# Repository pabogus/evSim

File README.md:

# Project evSim 
## Purpose description
Simulate a ev connected to a Wallbox for testing purposes.

For testing the behaviour of a AC walbox, respecively charging station, for e-mobility a car simulator is needed.
This project aims to provide such a simulator. In addition for test automation this simulator can be controlled via modbus protocoll using a RS485 connection.
You should be aware about the ISO states and the underlying physical protocoll used on the CS and PP line of a type-2 conector.

The project uses a attiny1616 controller to switch a couple of relays to simulate the voltage levels on the signal lines.
The relais are driven by a TPIC6B595 shift register which has the capability to drive the relays.
The RS485 lines are driven by a MAX 485 ECSA transmitter. The PWM is injected via an optocoppler  LTV 817B.

## As user interface there are:
Two buttons to switch states and cable attributes
An OLED display for the states and the measured PWM duty cycle
ws2812 like LED stripe also to indicate states and PWM duty cycle, respectively the current level.

## Schematic and PCB:
The project contains also a schematic and a PCB in KiCad format with the following features:
The evSim contains also an additional FET incl. a flyback diode, to drive an external releay, e.g. to switch the Walbox on and off.
The evSim provides an additional input at the plug connector intended for current on check.
The evSim contains two simulatior entities to be able to test a twin wallbox.
The evSim contains a voltage regulator for 5V to be independant of the power supply.
The evSim contains a coding switch for the modbus-ID.

For connection screw connectors are used.

### Note:
Currently this is done as a prototype and for usage in a real test environment the following improvements could be done.
- Add some more Cs or Ls for hardening against radiation and spikes.
- Add bigger voltage regulator, or use a tree pin DC/DC converter.
- Make PCB a bit larger, avoid SMD on the backside, add proper conector for power, Modbus and additional functions.

## Not tested/implemented yet:
Additional FET
Selection of modbus-ID via coding switch. Idea is to double use some GPIO lines and read the input at start-up.
Some supporting modbus registers.
Read in voltage on phase L1 with FinA/FinB, just with an opto and capacitive devider to be able to check that the walbox has realy turned on power. (But caution here you touch high volate, I would place the opto and devider on a separate small PCB)

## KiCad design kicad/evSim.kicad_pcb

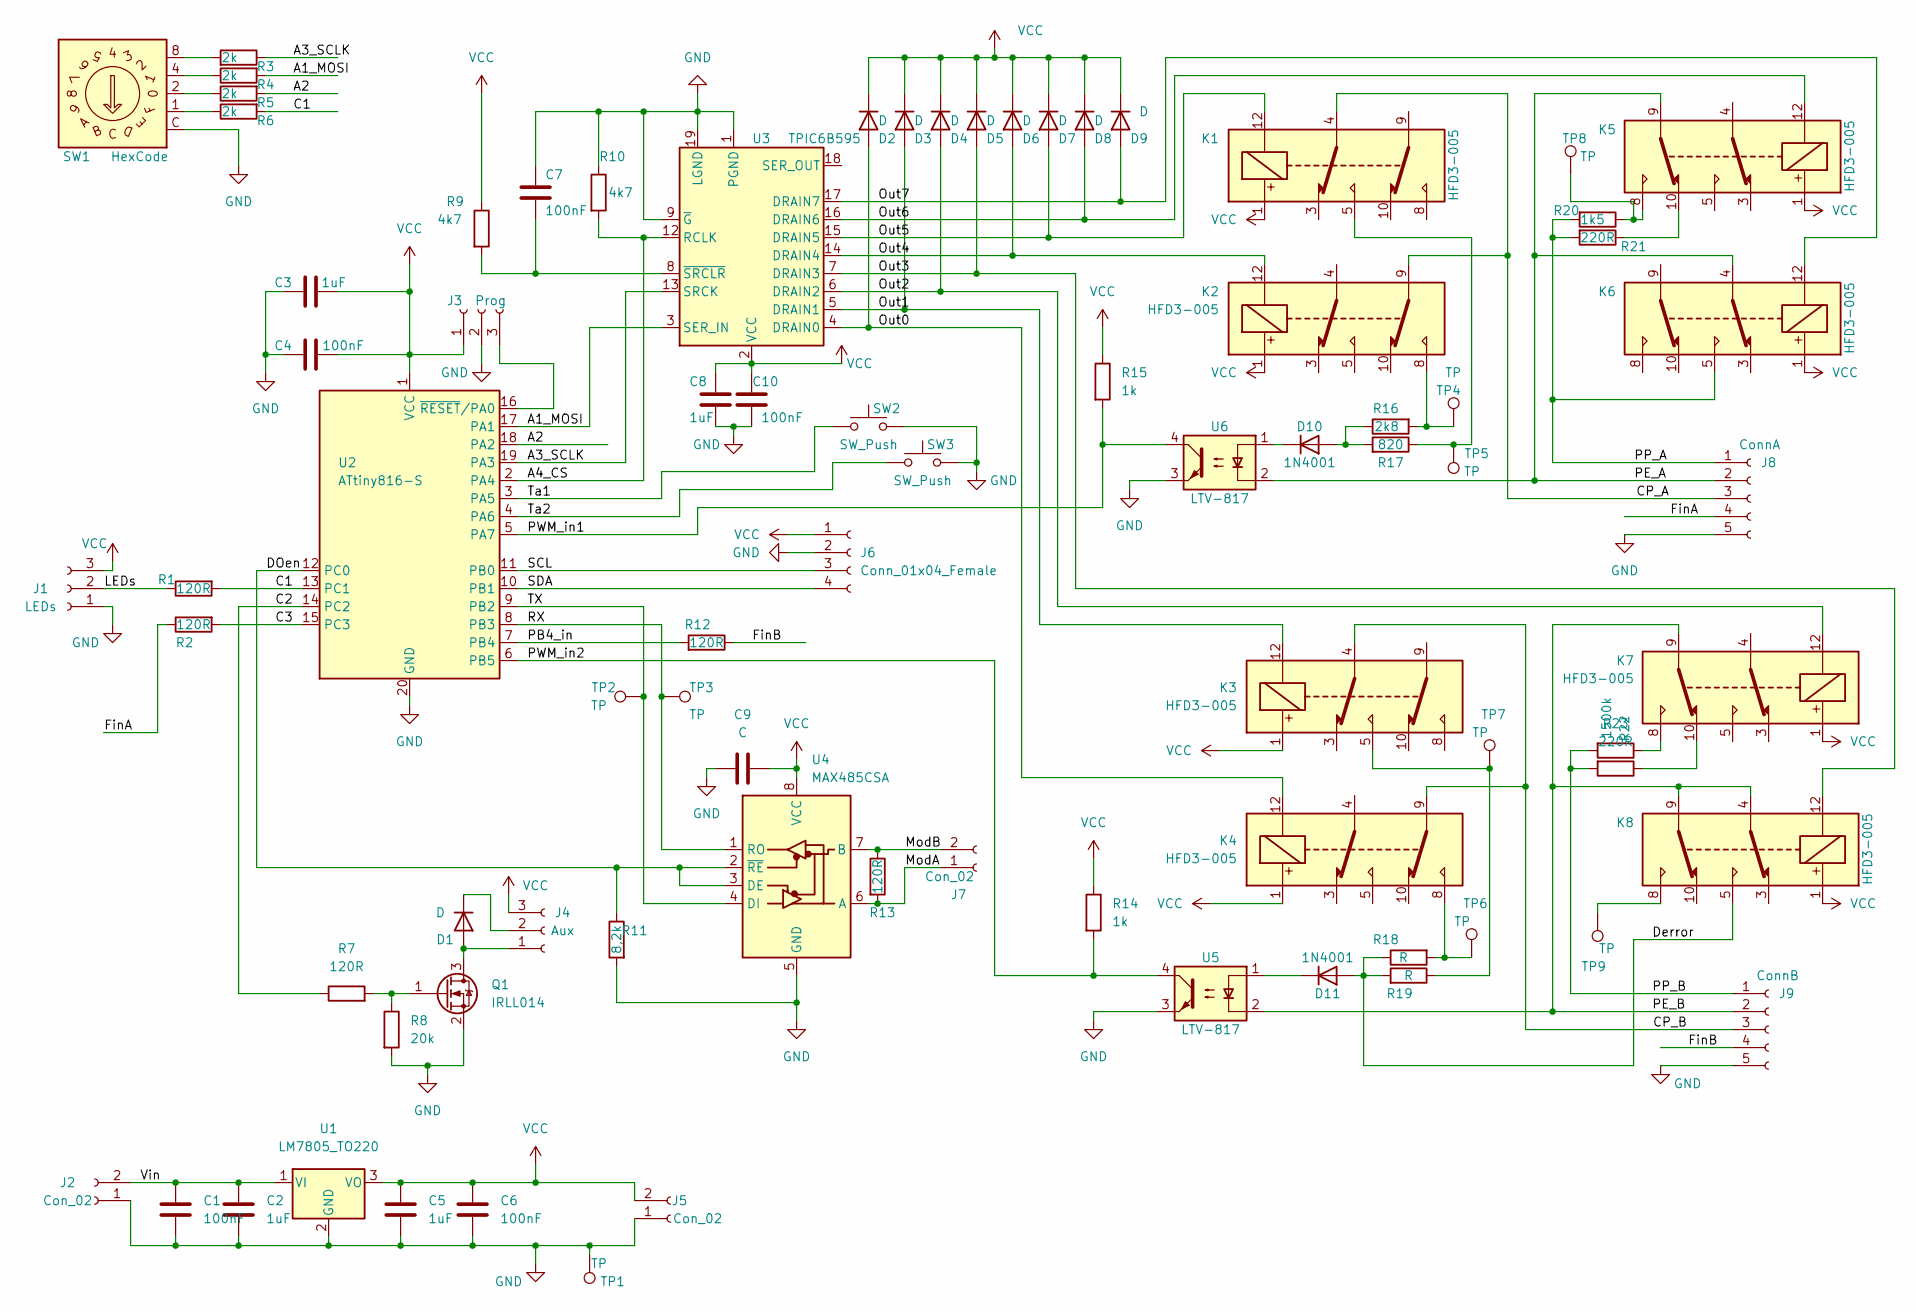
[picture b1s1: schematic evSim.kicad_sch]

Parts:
C1, C4, C7, C10: 100nF; C_0805_2012Metric_Pad1.18x1.45mm_HandSolder
C2, C5, C8: 1uF; C_0805_2012Metric_Pad1.18x1.45mm_HandSolder
C3: 1uF; C_Disc_D4.7mm_W2.5mm_P5.00mm
C6: 100nF; C_1206_3216Metric_Pad1.33x1.80mm_HandSolder
C9: C; C_0805_2012Metric_Pad1.18x1.45mm_HandSolder
D1: D; D_SMA_Handsoldering
D2, D3, D4, D5, D6, D7, D8, D9: D; D_A-405_P5.08mm_Vertical_AnodeUp
D10, D11: 1N4001; D_A-405_P2.54mm_Vertical_AnodeUp
J1: LEDs; PinHeader_1x03_P2.54mm_Vertical
J2, J5, J7: Con_02; PinHeader_1x02_P2.54mm_Vertical
J3: Prog; PinHeader_1x03_P2.54mm_Vertical
J4: Aux; PinHeader_1x03_P2.54mm_Vertical
J6: Conn_01x04_Female; PinHeader_1x04_P2.54mm_Vertical
J8: ConnA; PhoenixContact_MCV_1,5_5-G-5.08_1x05_P5.08mm_Vertical
J9: ConnB; PhoenixContact_MCV_1,5_5-G-5.08_1x05_P5.08mm_Vertical
K1, K2, K3, K4, K5, K6, K7, K8: HFD3-005; Relay_DPDT_Kemet_EC2
Q1: IRLL014; SOT-23
R1, R2, R7, R12: 120R; R_1206_3216Metric_Pad1.30x1.75mm_HandSolder
R3, R4, R5, R6: 2k; R_1206_3216Metric_Pad1.30x1.75mm_HandSolder
R8: 20k; R_1206_3216Metric_Pad1.30x1.75mm_HandSolder
R9, R10: 4k7; R_1206_3216Metric_Pad1.30x1.75mm_HandSolder
R11: 8,2k; R_1206_3216Metric_Pad1.30x1.75mm_HandSolder
R13: 120R; R_Axial_DIN0207_L6.3mm_D2.5mm_P7.62mm_Horizontal
R14, R15: 1k; R_1206_3216Metric_Pad1.30x1.75mm_HandSolder
R16: 2k8; R_Axial_DIN0207_L6.3mm_D2.5mm_P7.62mm_Horizontal
R17: 820; R_Axial_DIN0207_L6.3mm_D2.5mm_P7.62mm_Horizontal
R18, R19: R; R_Axial_DIN0207_L6.3mm_D2.5mm_P7.62mm_Horizontal
R20: 1k5; R_Axial_DIN0207_L6.3mm_D2.5mm_P7.62mm_Horizontal
R21, R23: 220R; R_Axial_DIN0207_L6.3mm_D2.5mm_P7.62mm_Horizontal
R22: 1500k; R_Axial_DIN0207_L6.3mm_D2.5mm_P7.62mm_Horizontal
SW1: HexCode; Nidec_Copal_SH-7010C
SW2, SW3: SW_Push; SW_SPST_B3S-1000
TP1, TP4, TP5, TP6, TP7, TP8, TP9: TP; TestPoint_Keystone_5000-5004_Miniature
TP2, TP3: TP; TestPoint_Pad_1.0x1.0mm
U1: LM7805_TO220; TO-252-3_TabPin2
U2: ATtiny816-S; SOIC-20W_7.5x12.8mm_P1.27mm
U3: TPIC6B595; DIP-20_W7.62mm
U4: MAX485CSA; SO-8_3.9x4.9mm_P1.27mm
U5, U6: LTV-817; DIP-4_W7.62mm

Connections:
/A1_MOSI: R4.2, U2.17 (PA1), U3.3 (SER_IN)
/A2: R5.2, U2.18 (PA2)
/A3_SCLK: R3.1, U2.19 (PA3), U3.13 (SRCK)
/A4_CS: R10.2, U2.2 (PA4), U3.12 (RCLK)
/C1: R1.2, R6.2, U2.13 (PC1)
/C2: R7.1, U2.14 (PC2)
/C3: R2.2, U2.15 (PC3)
/CP_A: J8.3, K1.4, K2.9
/CP_B: J9.3, K3.4, K4.9
/DOen: R11.1, U2.12 (PC0), U4.2 (~RE), U4.3 (DE)
/Derror: D11.2 (A), K8.5, R18.1, R19.2
/FinA: J8.4, R2.1
/FinB: J9.4, R12.1
/LEDs: J1.2, R1.1
/ModA: J7.1, R13.2, U4.6 (A)
/ModB: J7.2, R13.1, U4.7 (B)
/Out0: D2.2 (A), K4.12, U3.4 (DRAIN0)
/Out1: D3.2 (A), K3.12, U3.5 (DRAIN1)
/Out2: D4.2 (A), K7.12, U3.6 (DRAIN2)
/Out3: D5.2 (A), K8.12, U3.7 (DRAIN3)
/Out4: D6.2 (A), K2.12, U3.14 (DRAIN4)
/Out5: D7.2 (A), K1.12, U3.15 (DRAIN5)
/Out6: D8.2 (A), K5.12, U3.16 (DRAIN6)
/Out7: D9.2 (A), K6.12, U3.17 (DRAIN7)
/PB4_in: R12.2, U2.7 (PB4)
/PE_A: J8.2, K5.9, K6.4, U6.2
/PE_B: J9.2, K7.9, K8.4, K8.9, U5.2
/PP_A: J8.1, K6.5, R20.2, R21.2
/PP_B: J9.1, R22.2, R23.2
/PWM_in1: R15.2, U2.5 (PA7), U6.4
/PWM_in2: R14.2, U2.6 (PB5), U5.4
/RX: TP3.1, U2.8 (PB3), U4.1 (RO)
/SCL: J6.3, U2.11 (PB0)
/SDA: J6.4, U2.10 (PB1)
/TX: TP2.1, U2.9 (PB2), U4.4 (DI)
/Ta1: SW2.1, U2.3 (PA5)
/Ta2: SW3.1, U2.4 (PA6)
/Vin: C1.1, C2.1, J2.2, U1.1 (VI)
GND: C1.2, C2.2, C3.1, C4.1, C5.2, C6.2, C7.1, C8.2, C9.1, C10.2, J1.1, J2.1, J3.2, J5.1, J6.2, J8.5, J9.5, Q1.2 (S), R8.2, R10.1, R11.2, SW1.C, SW2.2, SW3.2, TP1.1, U1.2 (GND), U2.20 (GND), U3.1 (PGND), U3.9 (~G), U3.10 (PGND), U3.11 (PGND), U3.19 (LGND), U3.20 (PGND), U4.5 (GND), U5.3, U6.3
unnamed: D1.2 (A), J4.1, Q1.3 (D)
unnamed: D1.1 (K), J4.2
unnamed: D10.2 (A), R16.1, R17.2
unnamed: D10.1 (K), U6.1
unnamed: D11.1 (K), U5.1
unnamed: J3.3, U2.16 (~RESET/PA0)
unnamed: K1.5, R17.1, TP5.1
unnamed: K2.8, R16.2, TP4.1
unnamed: K3.5, R19.1, TP7.1
unnamed: K4.8, R18.2, TP6.1
unnamed: K5.8, R20.1, TP8.1
unnamed: K5.10, R21.1
unnamed: K7.8, R22.1
unnamed: K7.10, R23.1
unnamed: K8.8, TP9.1
unnamed: Q1.1 (G), R7.2, R8.1
unnamed: R3.2, SW1.8
unnamed: R4.1, SW1.4
unnamed: R5.1, SW1.2
unnamed: R6.1, SW1.1
unnamed: C7.2, R9.2, U3.8 (~SRCLR)
VCC: C3.2, C4.2, C5.1, C6.1, C8.1, C9.2, C10.1, D2.1 (K), D3.1 (K), D4.1 (K), D5.1 (K), D6.1 (K), D7.1 (K), D8.1 (K), D9.1 (K), J1.3, J3.1, J4.3, J5.2, J6.1, K1.1, K2.1, K3.1, K4.1, K5.1, K6.1, K7.1, K8.1, R9.1, R14.1, R15.1, U1.3 (VO), U2.1 (VCC), U3.2 (VCC), U4.8 (VCC)

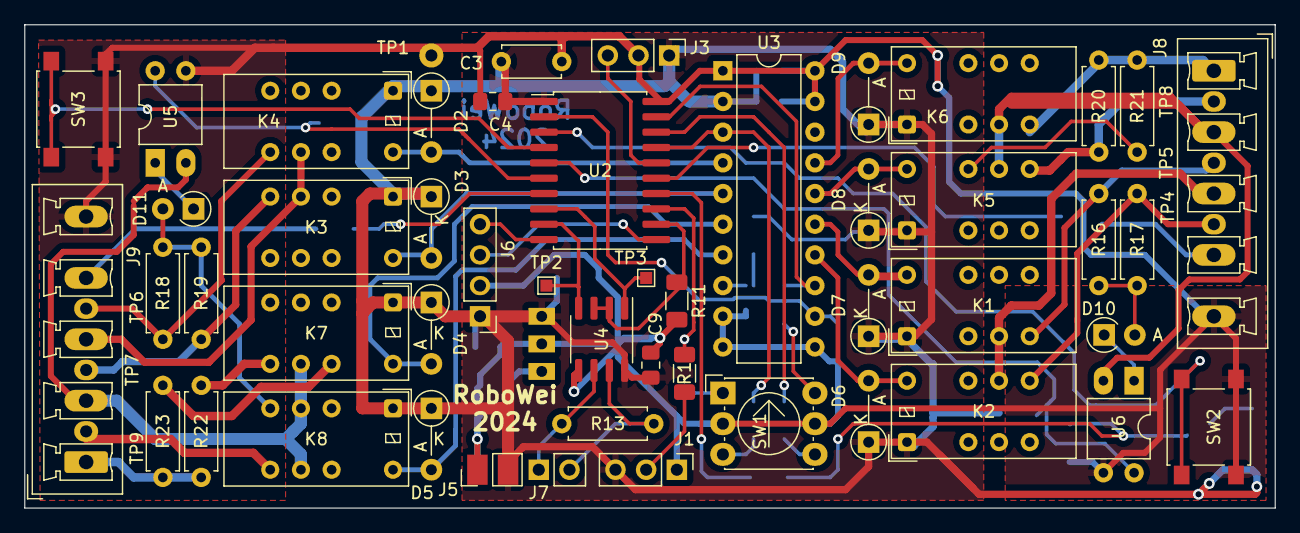
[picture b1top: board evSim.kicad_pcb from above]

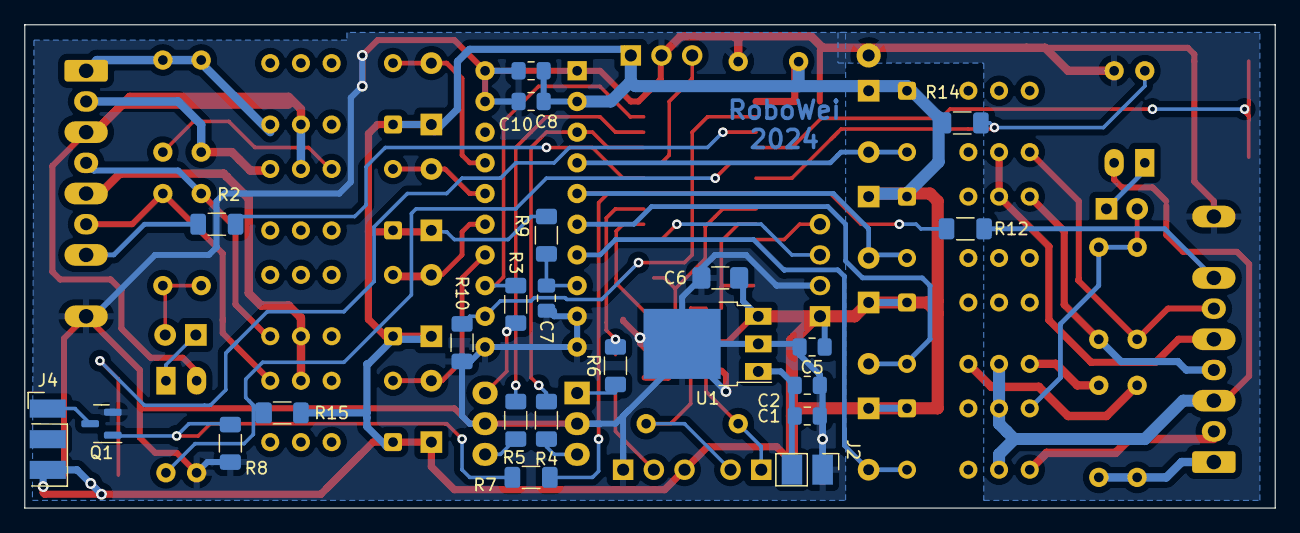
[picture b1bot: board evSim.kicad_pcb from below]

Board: 2 copper layers, 103.5 x 40.0 mm, 79 parts (23 on the bottom side), 60 nets.

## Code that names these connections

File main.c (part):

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             AtTiny1616
                _____
            Vcc-|   |-Gnd
      CS -- PA4-|   |-PA3 --SCLK
    TA_A -- PA5-|   |-PA2 --
    TA_B -- PA6-|   |-PA1 --MOSI
   PWM_A -- PA7-|   |-Reset/UPDI
   PWM_B --´PB5-|   |-PC3 --
         -- PB4-|   |-PC2 --
     RxD -- PB3-|   |-PC1 --LEDs
     TxD -- PB2-|   |-PC0 --RXen
     SDA -- PB1-|   |-PB0 --SCL
                -----

PCB setup: 
             AtTiny1616
                _____
            Vcc-|   |-Gnd
      CS -- PA4-|   |-PA3 --SCLK
    TA_A -- PA5-|   |-PA2 --
    TA_B -- PA6-|   |-PA1 --MOSI
   PWM_A -- PA7-|   |-Reset/UPDI
   PWM_B --´PB5-|   |-PC3 --Fin_A
   Fin_B -- PB4-|   |-PC2 --Aux_FET
     RxD -- PB3-|   |-PC1 --LEDs
     TxD -- PB2-|   |-PC0 --RXen
     SDA -- PB1-|   |-PB0 --SCL
                -----


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{
  PORTA.PIN7CTRL = PORT_INVEN_bm;    // Invert input

  PORTA.PIN5CTRL = PORT_PULLUPEN_bm; // Enable Pullup for PA5
  PORTA.PIN6CTRL = PORT_PULLUPEN_bm; // Enable Pullup for PA6
}

/**************************************************************
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
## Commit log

2025-08-05 Initial commit, project evSim
2025-08-12 Add kicad files for prototype a board
2025-08-12 Add description in README.md

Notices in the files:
main.c:
Copyright (C) 2025 pabogus <https://github.com/pabogus>
This program is free software: you can redistribute it and/or modify
it under the terms of the GNU Affero General Public License as published
